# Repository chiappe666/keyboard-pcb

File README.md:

# keyboard-pcb
 pcb for my keyboard

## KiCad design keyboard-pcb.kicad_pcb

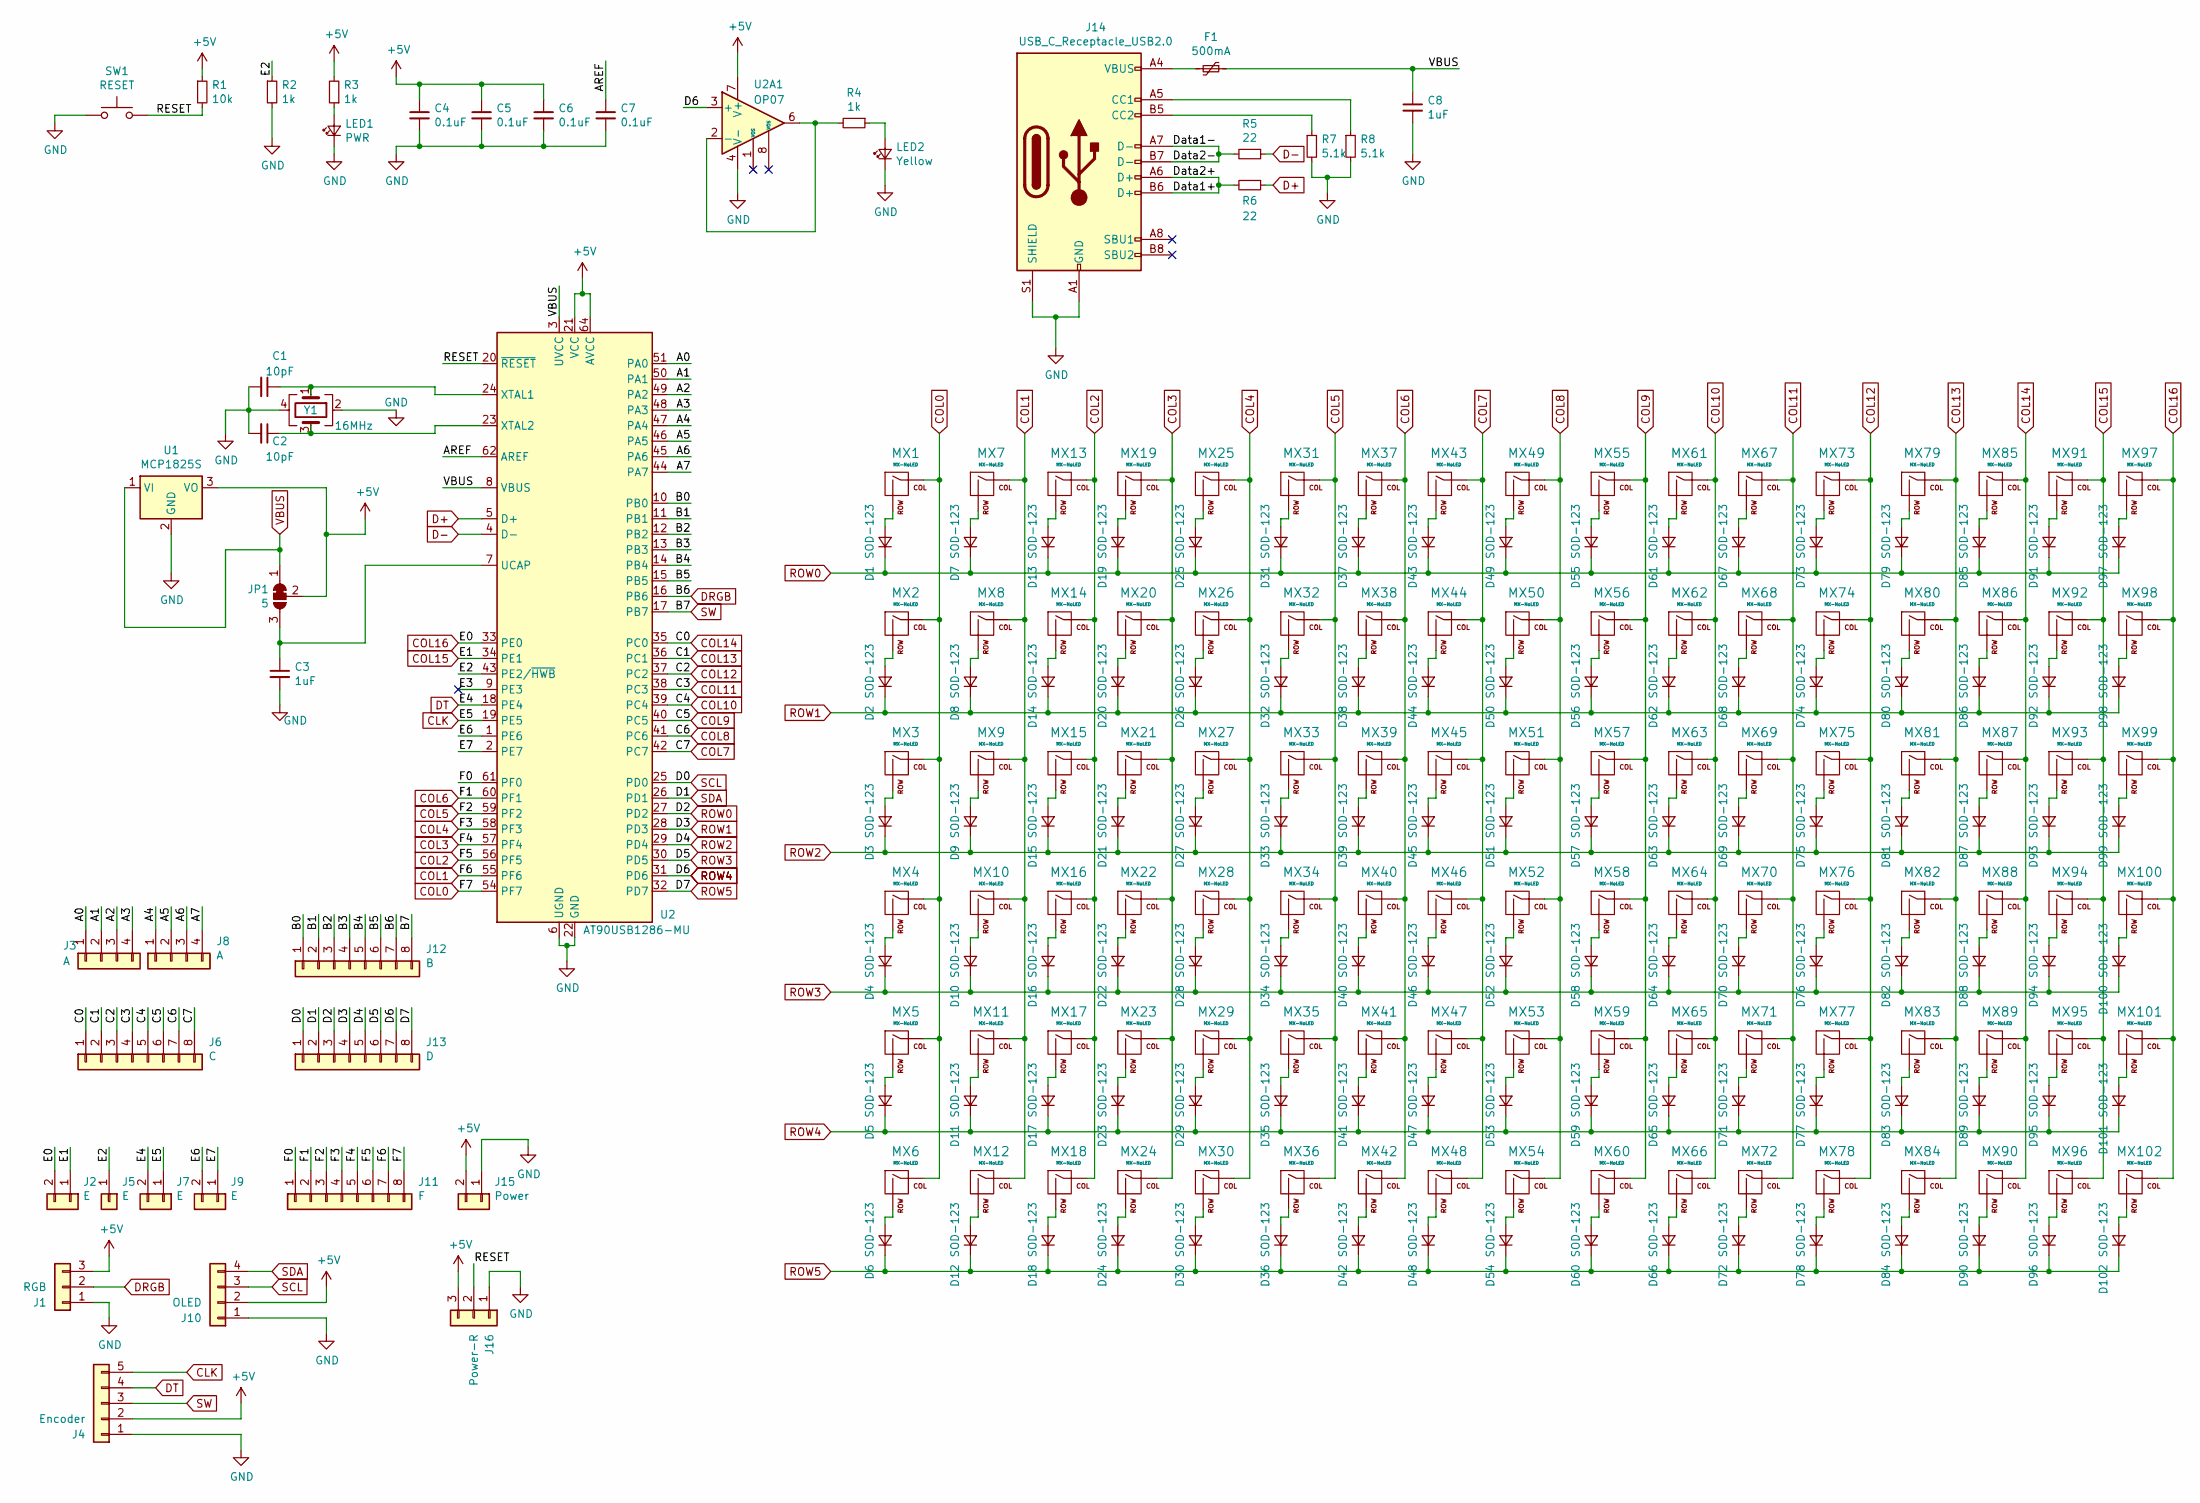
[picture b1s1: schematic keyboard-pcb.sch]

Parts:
C1, C2: 10pF; C_0603_1608Metric; LCSC C1634
C3, C8: 1uF; C_0603_1608Metric; LCSC C15849
C4, C5, C6, C7: 0.1uF; C_0603_1608Metric; LCSC C14663
D1, D2, D3, D4, D5, D6, D7, D8, D9, D10, D11, D12, D13, D14, D15, D16, D17, D18, D19, D20, D21, D22, D23, D24, D25, D26, D27, D28, D29, D30, D31, D32, D33, D34, D35, D36, D37, D38, D39, D40, D41, D42, D43, D44, D45, D46, D47, D48, D49, D50, D51, D52, D53, D54, D55, D56, D57, D58, D59, D60, D61, D62, D63, D64, D65, D66, D67, D68, D69, D70, D71, D72, D73, D74, D75, D76, D77, D78, D79, D80, D81, D82, D83, D84, D85, D86, D87, D88, D89, D90, D91, D92, D93, D94, D95, D96, D97, D98, D99, D100, D101, D102: SOD-123; D_SOD-123-Pretty; LCSC C81598
F1: 500mA; Fuse_0603_1608Metric; LCSC C2757929
J1: RGB; PinHeader_1x03_P1.00mm_Vertical
J2, J7, J9: E; PinHeader_1x02_P1.00mm_Vertical
J3, J8: A; PinHeader_1x04_P1.00mm_Vertical
J4: Encoder; PinHeader_1x05_P1.00mm_Vertical
J5: E; PinHeader_1x01_P1.00mm_Vertical
J6: C; PinHeader_1x08_P1.00mm_Vertical
J10: OLED; PinHeader_1x04_P1.00mm_Vertical
J11: F; PinHeader_1x08_P1.00mm_Vertical
J12: B; PinHeader_1x08_P1.00mm_Vertical
J13: D; PinHeader_1x08_P1.00mm_Vertical
J14: USB_C_Receptacle_USB2.0; USB_C_Receptacle_HRO_TYPE-C-31-M-12; LCSC C165948
J15: Power; PinHeader_1x02_P1.00mm_Vertical
J16: Power-R; PinHeader_1x03_P1.00mm_Vertical
JP1: 5; SolderJumper-3_P1.3mm_Bridged12_Pad1.0x1.5mm_NumberLabels
LED1: PWR; LED_0201_0603Metric; LCSC C72041
LED2: Yellow; LED_0201_0603Metric; LCSC C72038
MX1, MX2, MX3, MX4, MX5, MX6, MX7, MX8, MX9, MX10, MX11, MX12, MX13, MX14, MX15, MX16, MX17, MX18, MX19, MX20, MX21, MX22, MX23, MX24, MX25, MX26, MX27, MX28, MX29, MX30, MX31, MX32, MX33, MX34, MX35, MX36, MX37, MX38, MX39, MX40, MX41, MX42, MX43, MX44, MX45, MX46, MX47, MX48, MX49, MX50, MX51, MX52, MX53, MX54, MX55, MX56, MX57, MX58, MX59, MX60, MX61, MX62, MX63, MX64, MX65, MX66, MX67, MX68, MX69, MX70, MX71, MX72, MX73, MX74, MX75, MX76, MX77, MX78, MX79, MX80, MX81, MX82, MX83, MX84, MX85, MX86, MX87, MX88, MX89, MX90, MX91, MX92, MX93, MX94, MX95, MX96, MX97, MX98, MX99, MX100, MX101, MX102: MX-NoLED; MXOnly-1U-Hotswap-Antishear
R1: 10k; R_0603_1608Metric; LCSC C25804
R2, R3, R4: 1k; R_0603_1608Metric; LCSC C21190
R5, R6: 22; R_0603_1608Metric; LCSC C23345
R7, R8: 5.1k; R_0603_1608Metric; LCSC C23186
SW1: RESET; 2Pin_microswitch
U1: MCP1825S; SOT-223-3_TabPin2
U2: AT90USB1286-MU; QFN-64-1EP_9x9mm_P0.5mm_EP7.5x7.5mm; LCSC C619147
U2A1: OP07; SOIC-8_3.9x4.9mm_P1.27mm; LCSC C7433
Y1: 16MHz; Crystal_SMD_3225-4Pin_3.2x2.5mm; LCSC C13738

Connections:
+5V: C4.1, C5.1, C6.1, J1.3, J4.2, J10.2, J15.2, J16.3, JP1.2 (C), R1.1, R3.2, U1.3 (VO), U2.21 (VCC), U2.52 (VCC), U2.64 (AVCC), U2A1.7 (V+)
/A0: J3.1, U2.51 (PA0)
/A1: J3.2, U2.50 (PA1)
/A2: J3.3, U2.49 (PA2)
/A3: J3.4, U2.48 (PA3)
/A4: J8.1, U2.47 (PA4)
/A5: J8.2, U2.46 (PA5)
/A6: J8.3, U2.45 (PA6)
/A7: J8.4, U2.44 (PA7)
/AREF: C7.1, U2.62 (AREF)
/B0: J12.1, U2.10 (PB0)
/B1: J12.2, U2.11 (PB1)
/B2: J12.3, U2.12 (PB2)
/B3: J12.4, U2.13 (PB3)
/B4: J12.5, U2.14 (PB4)
/B5: J12.6, U2.15 (PB5)
/Data1+: J14.A6 (D+), J14.B6 (D+), R6.2
/Data1-: J14.A7 (D-), J14.B7 (D-), R5.2
/E2: J5.1, R2.1, U2.43 (PE2/~HWB)
/E6: J9.2, U2.1 (PE6)
/E7: J9.1, U2.2 (PE7)
/F0: J11.1, U2.61 (PF0)
/RESET: J16.2, R1.2, SW1.2, U2.20 (~RESET)
CLK: J4.5, J7.1, U2.19 (PE5)
COL0: J11.8, MX1.1 (COL), MX2.1 (COL), MX3.1 (COL), MX4.1 (COL), MX5.1 (COL), MX6.1 (COL), U2.54 (PF7)
COL1: J11.7, MX7.1 (COL), MX8.1 (COL), MX9.1 (COL), MX10.1 (COL), MX11.1 (COL), MX12.1 (COL), U2.55 (PF6)
COL2: J11.6, MX13.1 (COL), MX14.1 (COL), MX15.1 (COL), MX16.1 (COL), MX17.1 (COL), MX18.1 (COL), U2.56 (PF5)
COL3: J11.5, MX19.1 (COL), MX20.1 (COL), MX21.1 (COL), MX22.1 (COL), MX23.1 (COL), MX24.1 (COL), U2.57 (PF4)
COL4: J11.4, MX25.1 (COL), MX26.1 (COL), MX27.1 (COL), MX28.1 (COL), MX29.1 (COL), MX30.1 (COL), U2.58 (PF3)
COL5: J11.3, MX31.1 (COL), MX32.1 (COL), MX33.1 (COL), MX34.1 (COL), MX35.1 (COL), MX36.1 (COL), U2.59 (PF2)
COL6: J11.2, MX37.1 (COL), MX38.1 (COL), MX39.1 (COL), MX40.1 (COL), MX41.1 (COL), MX42.1 (COL), U2.60 (PF1)
COL7: J6.8, MX43.1 (COL), MX44.1 (COL), MX45.1 (COL), MX46.1 (COL), MX47.1 (COL), MX48.1 (COL), U2.42 (PC7)
COL8: J6.7, MX49.1 (COL), MX50.1 (COL), MX51.1 (COL), MX52.1 (COL), MX53.1 (COL), MX54.1 (COL), U2.41 (PC6)
COL9: J6.6, MX55.1 (COL), MX56.1 (COL), MX57.1 (COL), MX58.1 (COL), MX59.1 (COL), MX60.1 (COL), U2.40 (PC5)
COL10: J6.5, MX61.1 (COL), MX62.1 (COL), MX63.1 (COL), MX64.1 (COL), MX65.1 (COL), MX66.1 (COL), U2.39 (PC4)
COL11: J6.4, MX67.1 (COL), MX68.1 (COL), MX69.1 (COL), MX70.1 (COL), MX71.1 (COL), MX72.1 (COL), U2.38 (PC3)
COL12: J6.3, MX73.1 (COL), MX74.1 (COL), MX75.1 (COL), MX76.1 (COL), MX77.1 (COL), MX78.1 (COL), U2.37 (PC2)
COL13: J6.2, MX79.1 (COL), MX80.1 (COL), MX81.1 (COL), MX82.1 (COL), MX83.1 (COL), MX84.1 (COL), U2.36 (PC1)
COL14: J6.1, MX85.1 (COL), MX86.1 (COL), MX87.1 (COL), MX88.1 (COL), MX89.1 (COL), MX90.1 (COL), U2.35 (PC0)
COL15: J2.1, MX91.1 (COL), MX92.1 (COL), MX93.1 (COL), MX94.1 (COL), MX95.1 (COL), MX96.1 (COL), U2.34 (PE1)
COL16: J2.2, MX97.1 (COL), MX98.1 (COL), MX99.1 (COL), MX100.1 (COL), MX101.1 (COL), MX102.1 (COL), U2.33 (PE0)
D+: R6.1, U2.5 (D+)
D-: R5.1, U2.4 (D-)
DRGB: J1.2, J12.7, U2.16 (PB6)
DT: J4.4, J7.2, U2.18 (PE4)
GND: C1.2, C2.2, C3.2, C4.2, C5.2, C6.2, C7.2, C8.2, J1.1, J4.1, J10.1, J14.A1 (GND), J14.A12 (GND), J14.B1 (GND), J14.B12 (GND), J14.S1 (SHIELD), J15.1, J16.1, LED1.1 (K), LED2.1 (K), R2.2, R7.2, R8.2, SW1.1, U1.2 (GND), U2.6 (UGND), U2.22 (GND), U2.53 (GND), U2.63 (GND), U2.65 (GND), U2A1.4 (V-), Y1.2, Y1.4
unnamed: C1.1, U2.24 (XTAL1), Y1.1
unnamed: C2.1, U2.23 (XTAL2), Y1.3
unnamed: C3.1, JP1.3 (B), U2.7 (UCAP)
unnamed: D1.2 (A), MX1.2 (ROW)
unnamed: D2.2 (A), MX2.2 (ROW)
unnamed: D3.2 (A), MX3.2 (ROW)
unnamed: D4.2 (A), MX4.2 (ROW)
unnamed: D5.2 (A), MX5.2 (ROW)
unnamed: D6.2 (A), MX6.2 (ROW)
unnamed: D7.2 (A), MX7.2 (ROW)
unnamed: D8.2 (A), MX8.2 (ROW)
unnamed: D9.2 (A), MX9.2 (ROW)
unnamed: D10.2 (A), MX10.2 (ROW)
unnamed: D11.2 (A), MX11.2 (ROW)
unnamed: D12.2 (A), MX12.2 (ROW)
unnamed: D13.2 (A), MX13.2 (ROW)
unnamed: D14.2 (A), MX14.2 (ROW)
unnamed: D15.2 (A), MX15.2 (ROW)
unnamed: D16.2 (A), MX16.2 (ROW)
unnamed: D17.2 (A), MX17.2 (ROW)
unnamed: D18.2 (A), MX18.2 (ROW)
unnamed: D19.2 (A), MX19.2 (ROW)
unnamed: D20.2 (A), MX20.2 (ROW)
unnamed: D21.2 (A), MX21.2 (ROW)
unnamed: D22.2 (A), MX22.2 (ROW)
unnamed: D23.2 (A), MX23.2 (ROW)
unnamed: D24.2 (A), MX24.2 (ROW)
unnamed: D25.2 (A), MX25.2 (ROW)
unnamed: D26.2 (A), MX26.2 (ROW)
unnamed: D27.2 (A), MX27.2 (ROW)
unnamed: D28.2 (A), MX28.2 (ROW)
unnamed: D29.2 (A), MX29.2 (ROW)
unnamed: D30.2 (A), MX30.2 (ROW)
unnamed: D31.2 (A), MX31.2 (ROW)
unnamed: D32.2 (A), MX32.2 (ROW)
unnamed: D33.2 (A), MX33.2 (ROW)
unnamed: D34.2 (A), MX34.2 (ROW)
unnamed: D35.2 (A), MX35.2 (ROW)
unnamed: D36.2 (A), MX36.2 (ROW)
unnamed: D37.2 (A), MX37.2 (ROW)
unnamed: D38.2 (A), MX38.2 (ROW)
unnamed: D39.2 (A), MX39.2 (ROW)
unnamed: D40.2 (A), MX40.2 (ROW)
unnamed: D41.2 (A), MX41.2 (ROW)
unnamed: D42.2 (A), MX42.2 (ROW)
unnamed: D43.2 (A), MX43.2 (ROW)
unnamed: D44.2 (A), MX44.2 (ROW)
unnamed: D45.2 (A), MX45.2 (ROW)
unnamed: D46.2 (A), MX46.2 (ROW)
unnamed: D47.2 (A), MX47.2 (ROW)
unnamed: D48.2 (A), MX48.2 (ROW)
unnamed: D49.2 (A), MX49.2 (ROW)
unnamed: D50.2 (A), MX50.2 (ROW)
unnamed: D51.2 (A), MX51.2 (ROW)
unnamed: D52.2 (A), MX52.2 (ROW)
unnamed: D53.2 (A), MX53.2 (ROW)
unnamed: D54.2 (A), MX54.2 (ROW)
unnamed: D55.2 (A), MX55.2 (ROW)
unnamed: D56.2 (A), MX56.2 (ROW)
unnamed: D57.2 (A), MX57.2 (ROW)
unnamed: D58.2 (A), MX58.2 (ROW)
unnamed: D59.2 (A), MX59.2 (ROW)
unnamed: D60.2 (A), MX60.2 (ROW)
unnamed: D61.2 (A), MX61.2 (ROW)
unnamed: D62.2 (A), MX62.2 (ROW)
unnamed: D63.2 (A), MX63.2 (ROW)
unnamed: D64.2 (A), MX64.2 (ROW)
unnamed: D65.2 (A), MX65.2 (ROW)
unnamed: D66.2 (A), MX66.2 (ROW)
unnamed: D67.2 (A), MX67.2 (ROW)
unnamed: D68.2 (A), MX68.2 (ROW)
unnamed: D69.2 (A), MX69.2 (ROW)
unnamed: D70.2 (A), MX70.2 (ROW)
unnamed: D71.2 (A), MX71.2 (ROW)
unnamed: D72.2 (A), MX72.2 (ROW)
unnamed: D73.2 (A), MX73.2 (ROW)
unnamed: D74.2 (A), MX74.2 (ROW)
unnamed: D75.2 (A), MX75.2 (ROW)
unnamed: D76.2 (A), MX76.2 (ROW)
unnamed: D77.2 (A), MX77.2 (ROW)
unnamed: D78.2 (A), MX78.2 (ROW)
unnamed: D79.2 (A), MX79.2 (ROW)
unnamed: D80.2 (A), MX80.2 (ROW)
unnamed: D81.2 (A), MX81.2 (ROW)
unnamed: D82.2 (A), MX82.2 (ROW)
unnamed: D83.2 (A), MX83.2 (ROW)
unnamed: D84.2 (A), MX84.2 (ROW)
unnamed: D85.2 (A), MX85.2 (ROW)
unnamed: D86.2 (A), MX86.2 (ROW)
unnamed: D87.2 (A), MX87.2 (ROW)
unnamed: D88.2 (A), MX88.2 (ROW)
unnamed: D89.2 (A), MX89.2 (ROW)
unnamed: D90.2 (A), MX90.2 (ROW)
unnamed: D91.2 (A), MX91.2 (ROW)
unnamed: D92.2 (A), MX92.2 (ROW)
unnamed: D93.2 (A), MX93.2 (ROW)
unnamed: D94.2 (A), MX94.2 (ROW)
unnamed: D95.2 (A), MX95.2 (ROW)
unnamed: D96.2 (A), MX96.2 (ROW)
unnamed: D97.2 (A), MX97.2 (ROW)
unnamed: D98.2 (A), MX98.2 (ROW)
unnamed: D99.2 (A), MX99.2 (ROW)
unnamed: D100.2 (A), MX100.2 (ROW)
unnamed: D101.2 (A), MX101.2 (ROW)
unnamed: D102.2 (A), MX102.2 (ROW)
unnamed: F1.2, J14.A4 (VBUS), J14.A9 (VBUS), J14.B4 (VBUS), J14.B9 (VBUS)
unnamed: J14.A5 (CC1), R8.1
unnamed: J14.B5 (CC2), R7.1
unnamed: LED1.2 (A), R3.1
unnamed: LED2.2 (A), R4.1
unnamed: R4.2, U2A1.2 (-), U2A1.6
ROW0: D1.1 (K), D7.1 (K), D13.1 (K), D19.1 (K), D25.1 (K), D31.1 (K), D37.1 (K), D43.1 (K), D49.1 (K), D55.1 (K), D61.1 (K), D67.1 (K), D73.1 (K), D79.1 (K), D85.1 (K), D91.1 (K), D97.1 (K), J13.3, U2.27 (PD2)
ROW1: D2.1 (K), D8.1 (K), D14.1 (K), D20.1 (K), D26.1 (K), D32.1 (K), D38.1 (K), D44.1 (K), D50.1 (K), D56.1 (K), D62.1 (K), D68.1 (K), D74.1 (K), D80.1 (K), D86.1 (K), D92.1 (K), D98.1 (K), J13.4, U2.28 (PD3)
ROW2: D3.1 (K), D9.1 (K), D15.1 (K), D21.1 (K), D27.1 (K), D33.1 (K), D39.1 (K), D45.1 (K), D51.1 (K), D57.1 (K), D63.1 (K), D69.1 (K), D75.1 (K), D81.1 (K), D87.1 (K), D93.1 (K), D99.1 (K), J13.5, U2.29 (PD4)
ROW3: D4.1 (K), D10.1 (K), D16.1 (K), D22.1 (K), D28.1 (K), D34.1 (K), D40.1 (K), D46.1 (K), D52.1 (K), D58.1 (K), D64.1 (K), D70.1 (K), D76.1 (K), D82.1 (K), D88.1 (K), D94.1 (K), D100.1 (K), J13.6, U2.30 (PD5)
ROW4: D5.1 (K), D11.1 (K), D17.1 (K), D23.1 (K), D29.1 (K), D35.1 (K), D41.1 (K), D47.1 (K), D53.1 (K), D59.1 (K), D65.1 (K), D71.1 (K), D77.1 (K), D83.1 (K), D89.1 (K), D95.1 (K), D101.1 (K), J13.7, U2.31 (PD6), U2A1.3 (+)
ROW5: D6.1 (K), D12.1 (K), D18.1 (K), D24.1 (K), D30.1 (K), D36.1 (K), D42.1 (K), D48.1 (K), D54.1 (K), D60.1 (K), D66.1 (K), D72.1 (K), D78.1 (K), D84.1 (K), D90.1 (K), D96.1 (K), D102.1 (K), J13.8, U2.32 (PD7)
SCL: J10.3, J13.1, U2.25 (PD0)
SDA: J10.4, J13.2, U2.26 (PD1)
SW: J4.3, J12.8, U2.17 (PB7)
VBUS: C8.1, F1.1, JP1.1 (A), U1.1 (VI), U2.3 (UVCC), U2.8 (VBUS)

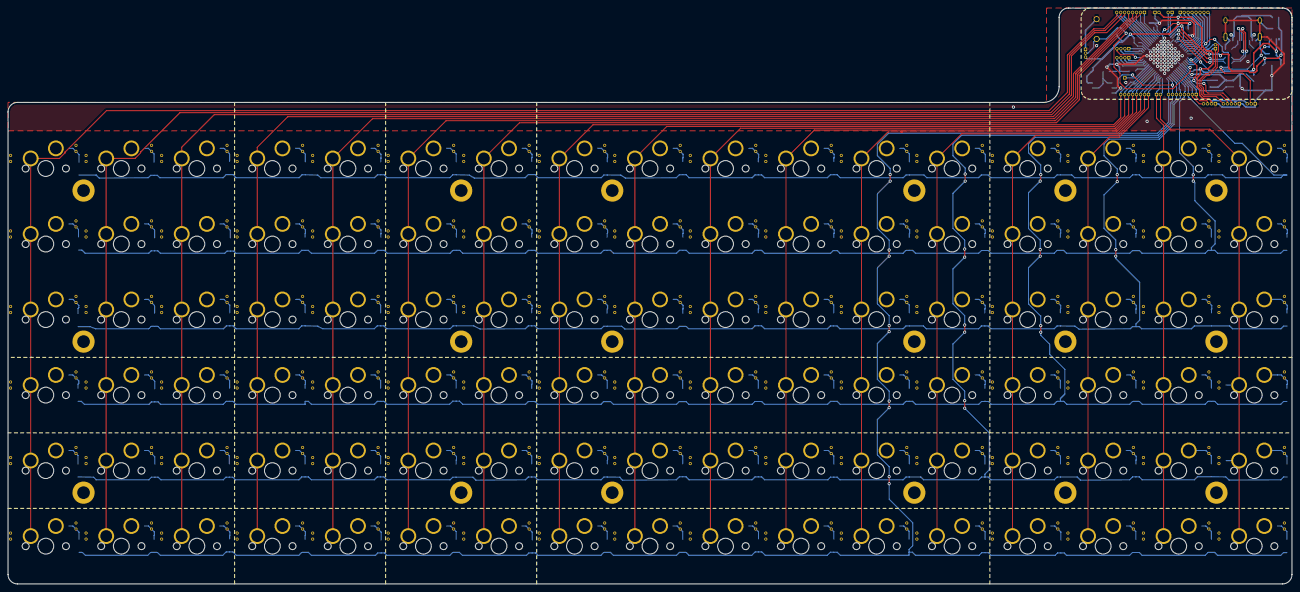
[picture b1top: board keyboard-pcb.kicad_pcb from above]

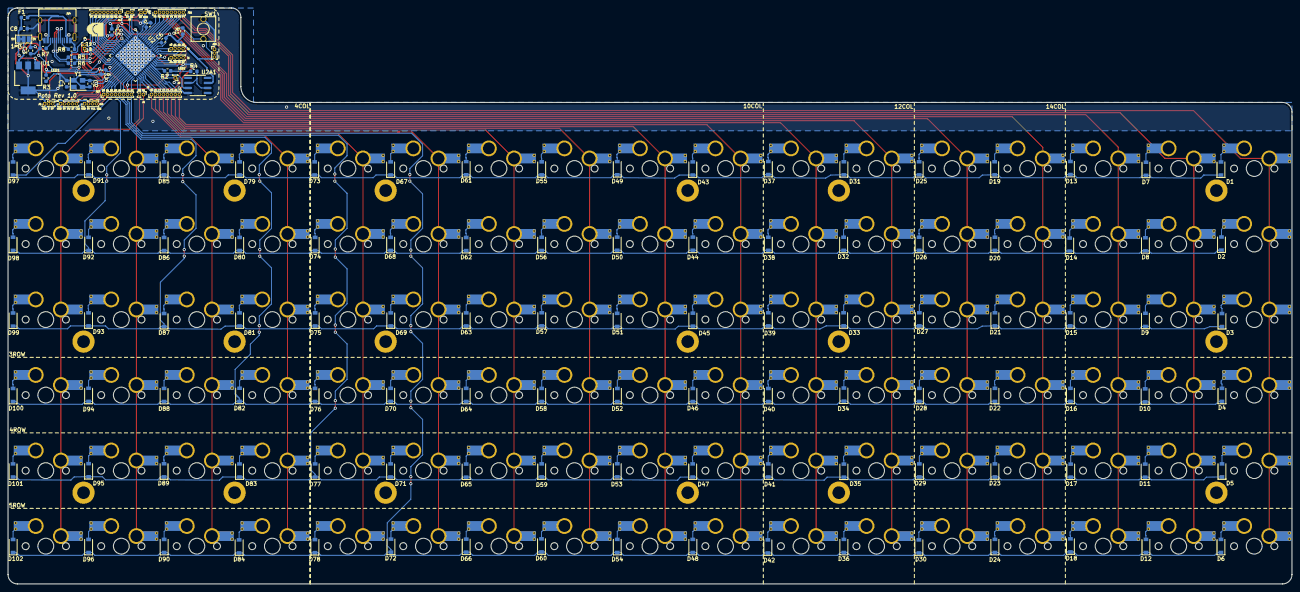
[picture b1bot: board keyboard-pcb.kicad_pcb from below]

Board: 2 copper layers, 323.9 x 145.3 mm, 245 parts (143 on the bottom side), 167 nets.

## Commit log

2021-07-10 Add submodules
2021-07-10 adding libraries
2021-07-11 Create fp-info-cache
2021-08-17 Change of MCU
    Now based on Teensy++ 2.0
2021-08-19 Schematic
    Schematic mostly done, i think
2021-08-19 Added fuse footprints
    added kicad updated fuse footprints
2021-09-13 Various changes
    Mostly done i think
2021-09-13 Gitignore
    added ignore
2021-09-13 Touching it up
    Added Fillzones and better Silkscreen
2021-09-14 added values for JLCPCB
    added field value for JLCPCB
2021-09-14 Cleaning
    Deleting some unused files
2021-09-14 Finished i think
    Changed names of files, finished silkscreen, some rearranging
2021-09-15 added gerbers
    added gerber files and some 3d models
2021-09-15 adding submodule
2021-09-15 fixes and 3d
    fixed libraries and added 3d models
2021-09-19 finished?
    rev1 finished
2021-09-19 things that were left
    i forgor
2021-09-19 ignore
2021-09-19 remove cached files
